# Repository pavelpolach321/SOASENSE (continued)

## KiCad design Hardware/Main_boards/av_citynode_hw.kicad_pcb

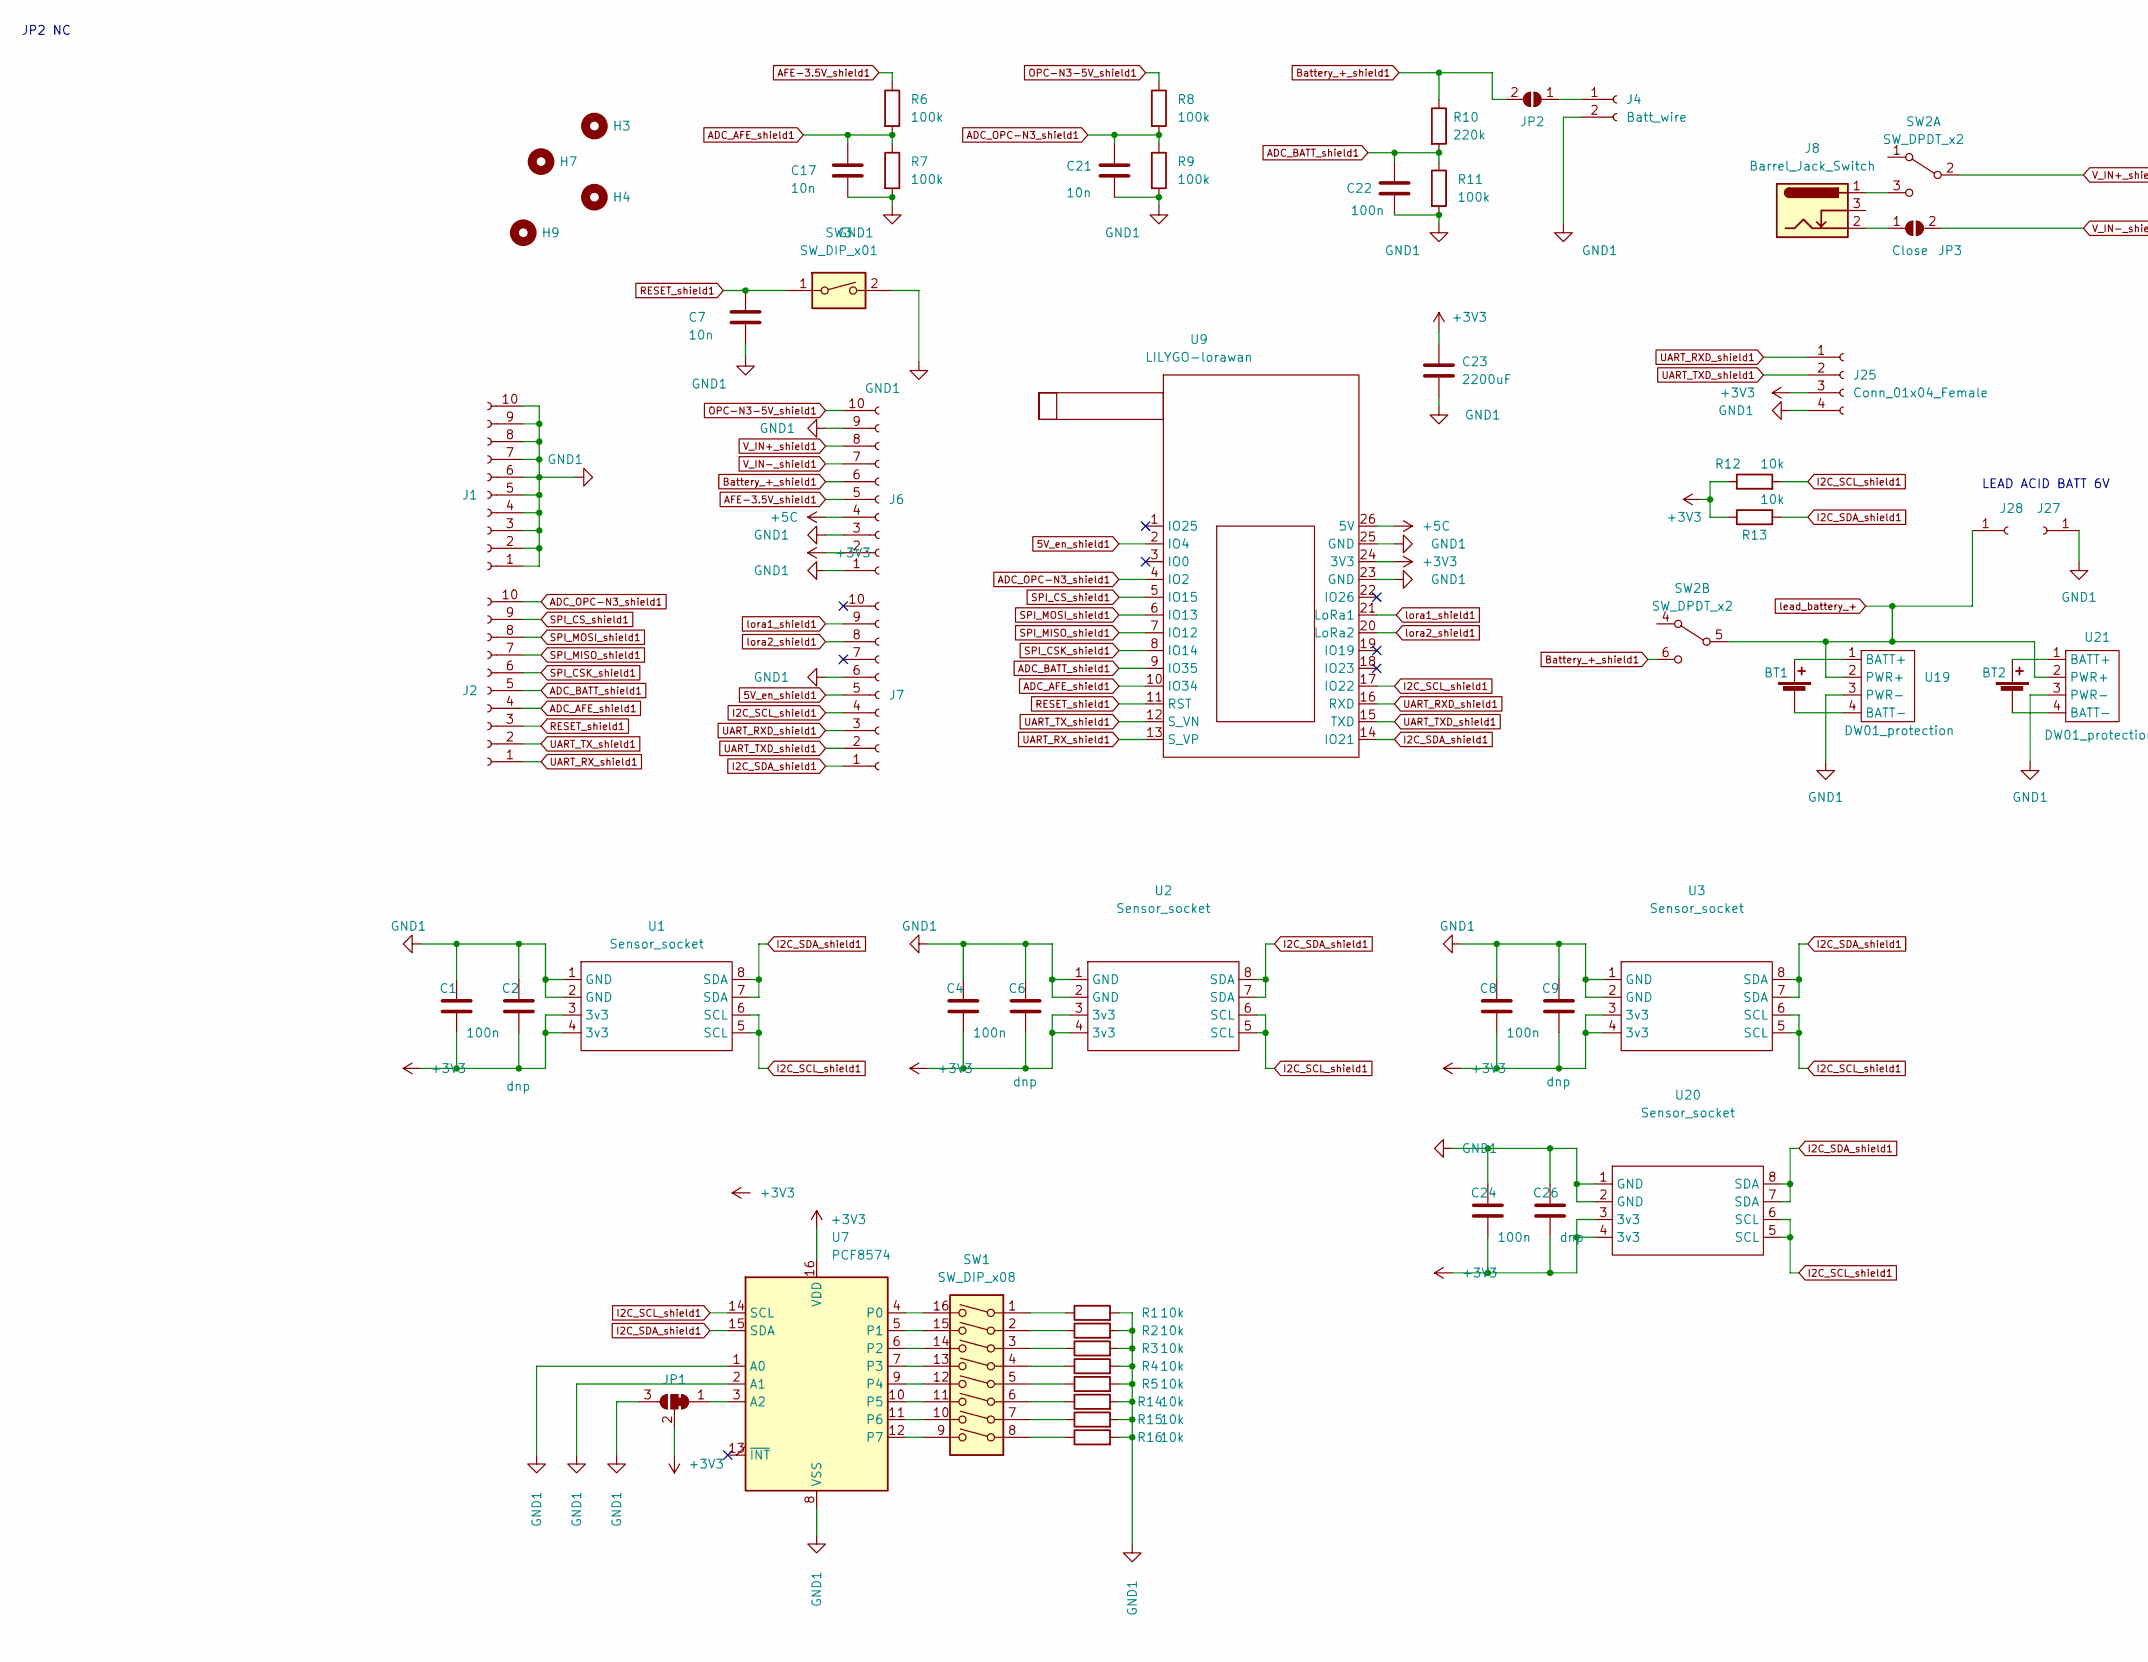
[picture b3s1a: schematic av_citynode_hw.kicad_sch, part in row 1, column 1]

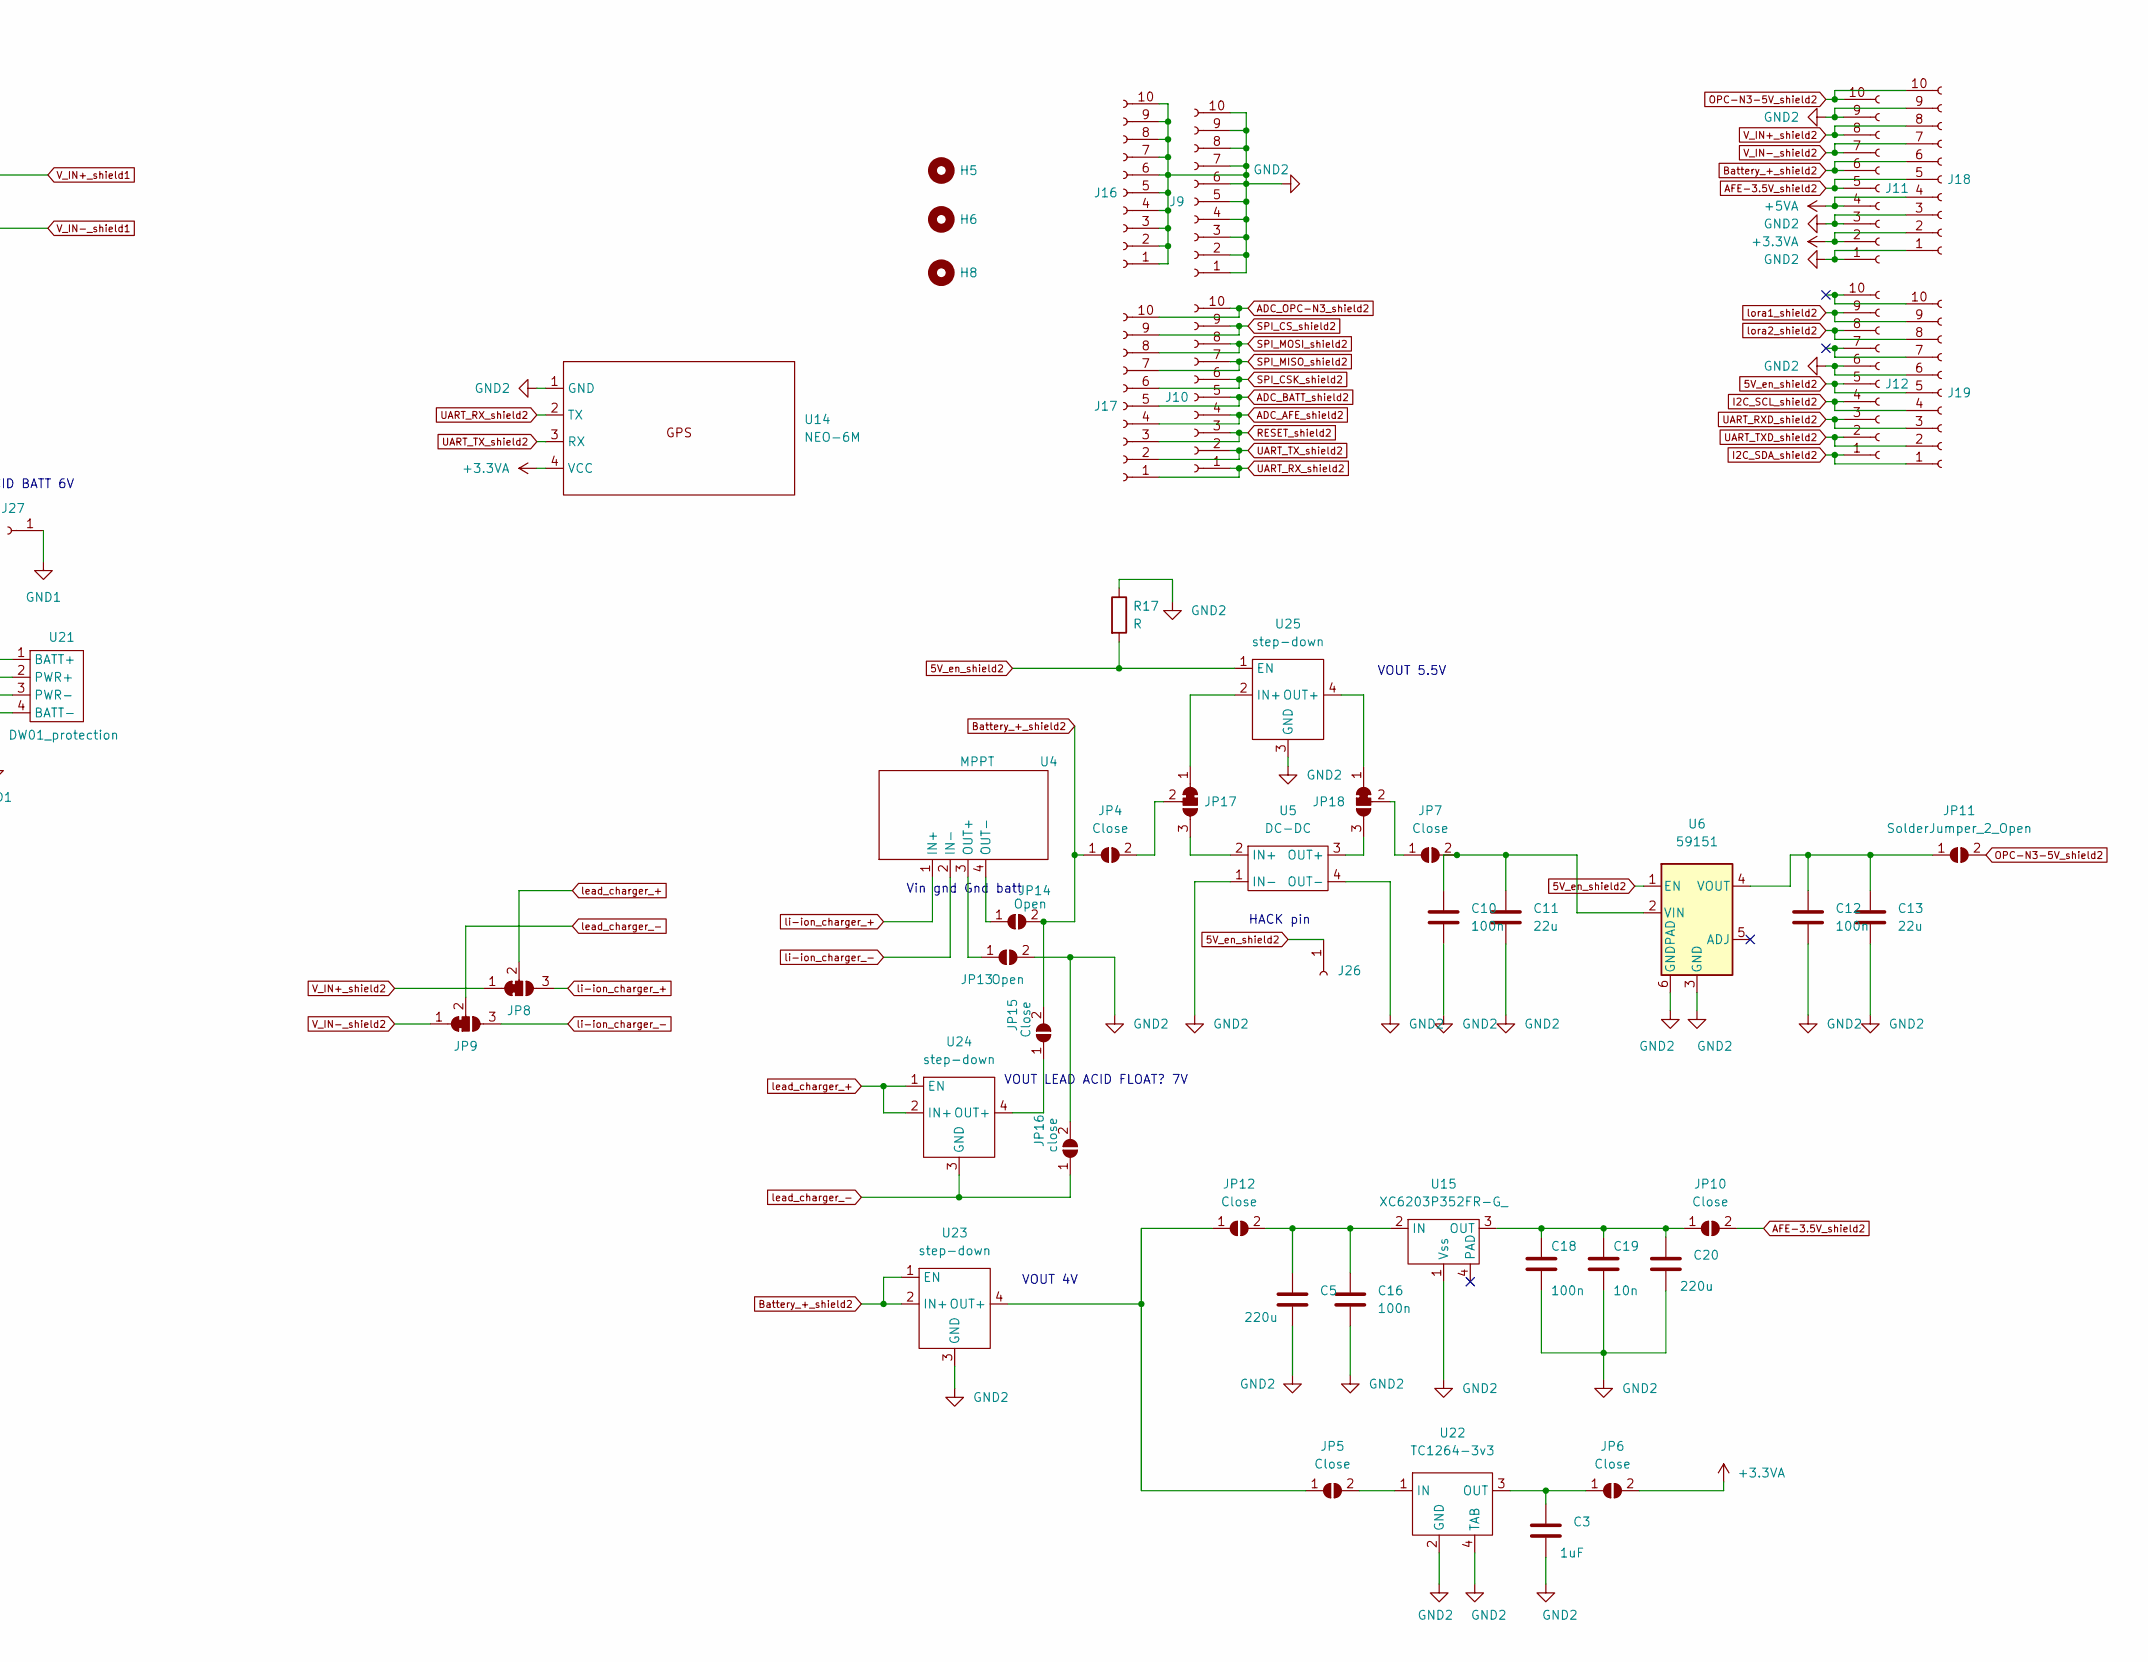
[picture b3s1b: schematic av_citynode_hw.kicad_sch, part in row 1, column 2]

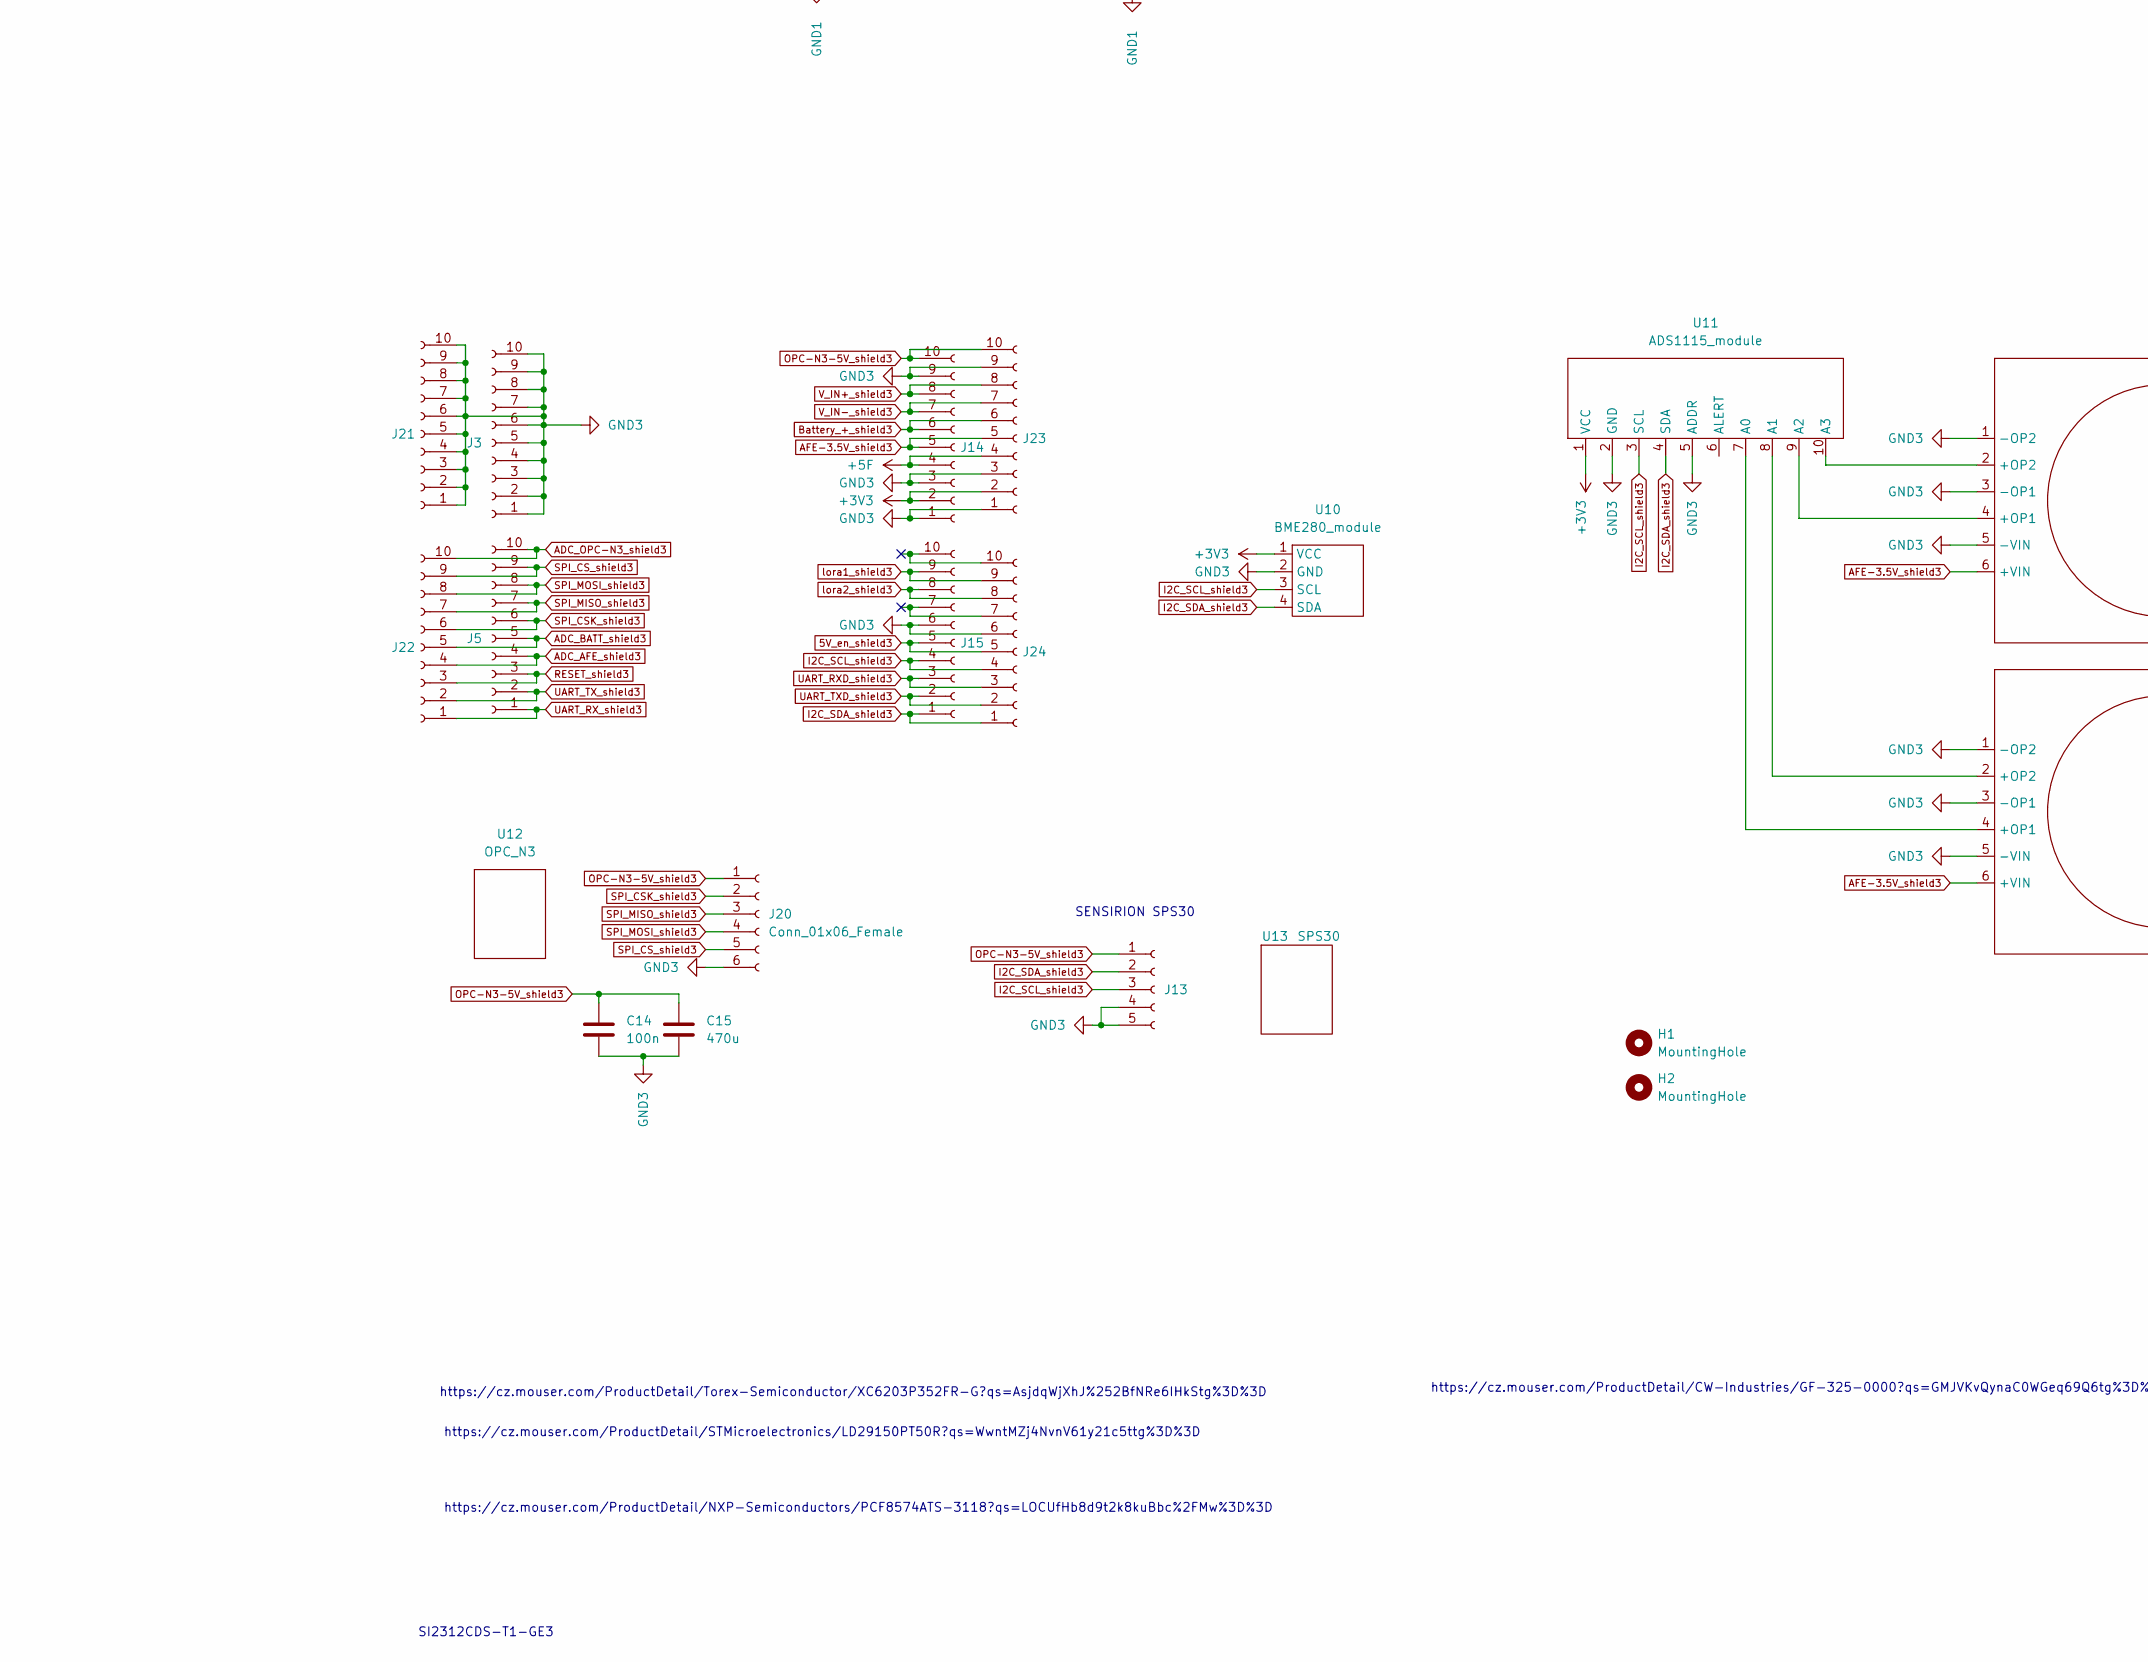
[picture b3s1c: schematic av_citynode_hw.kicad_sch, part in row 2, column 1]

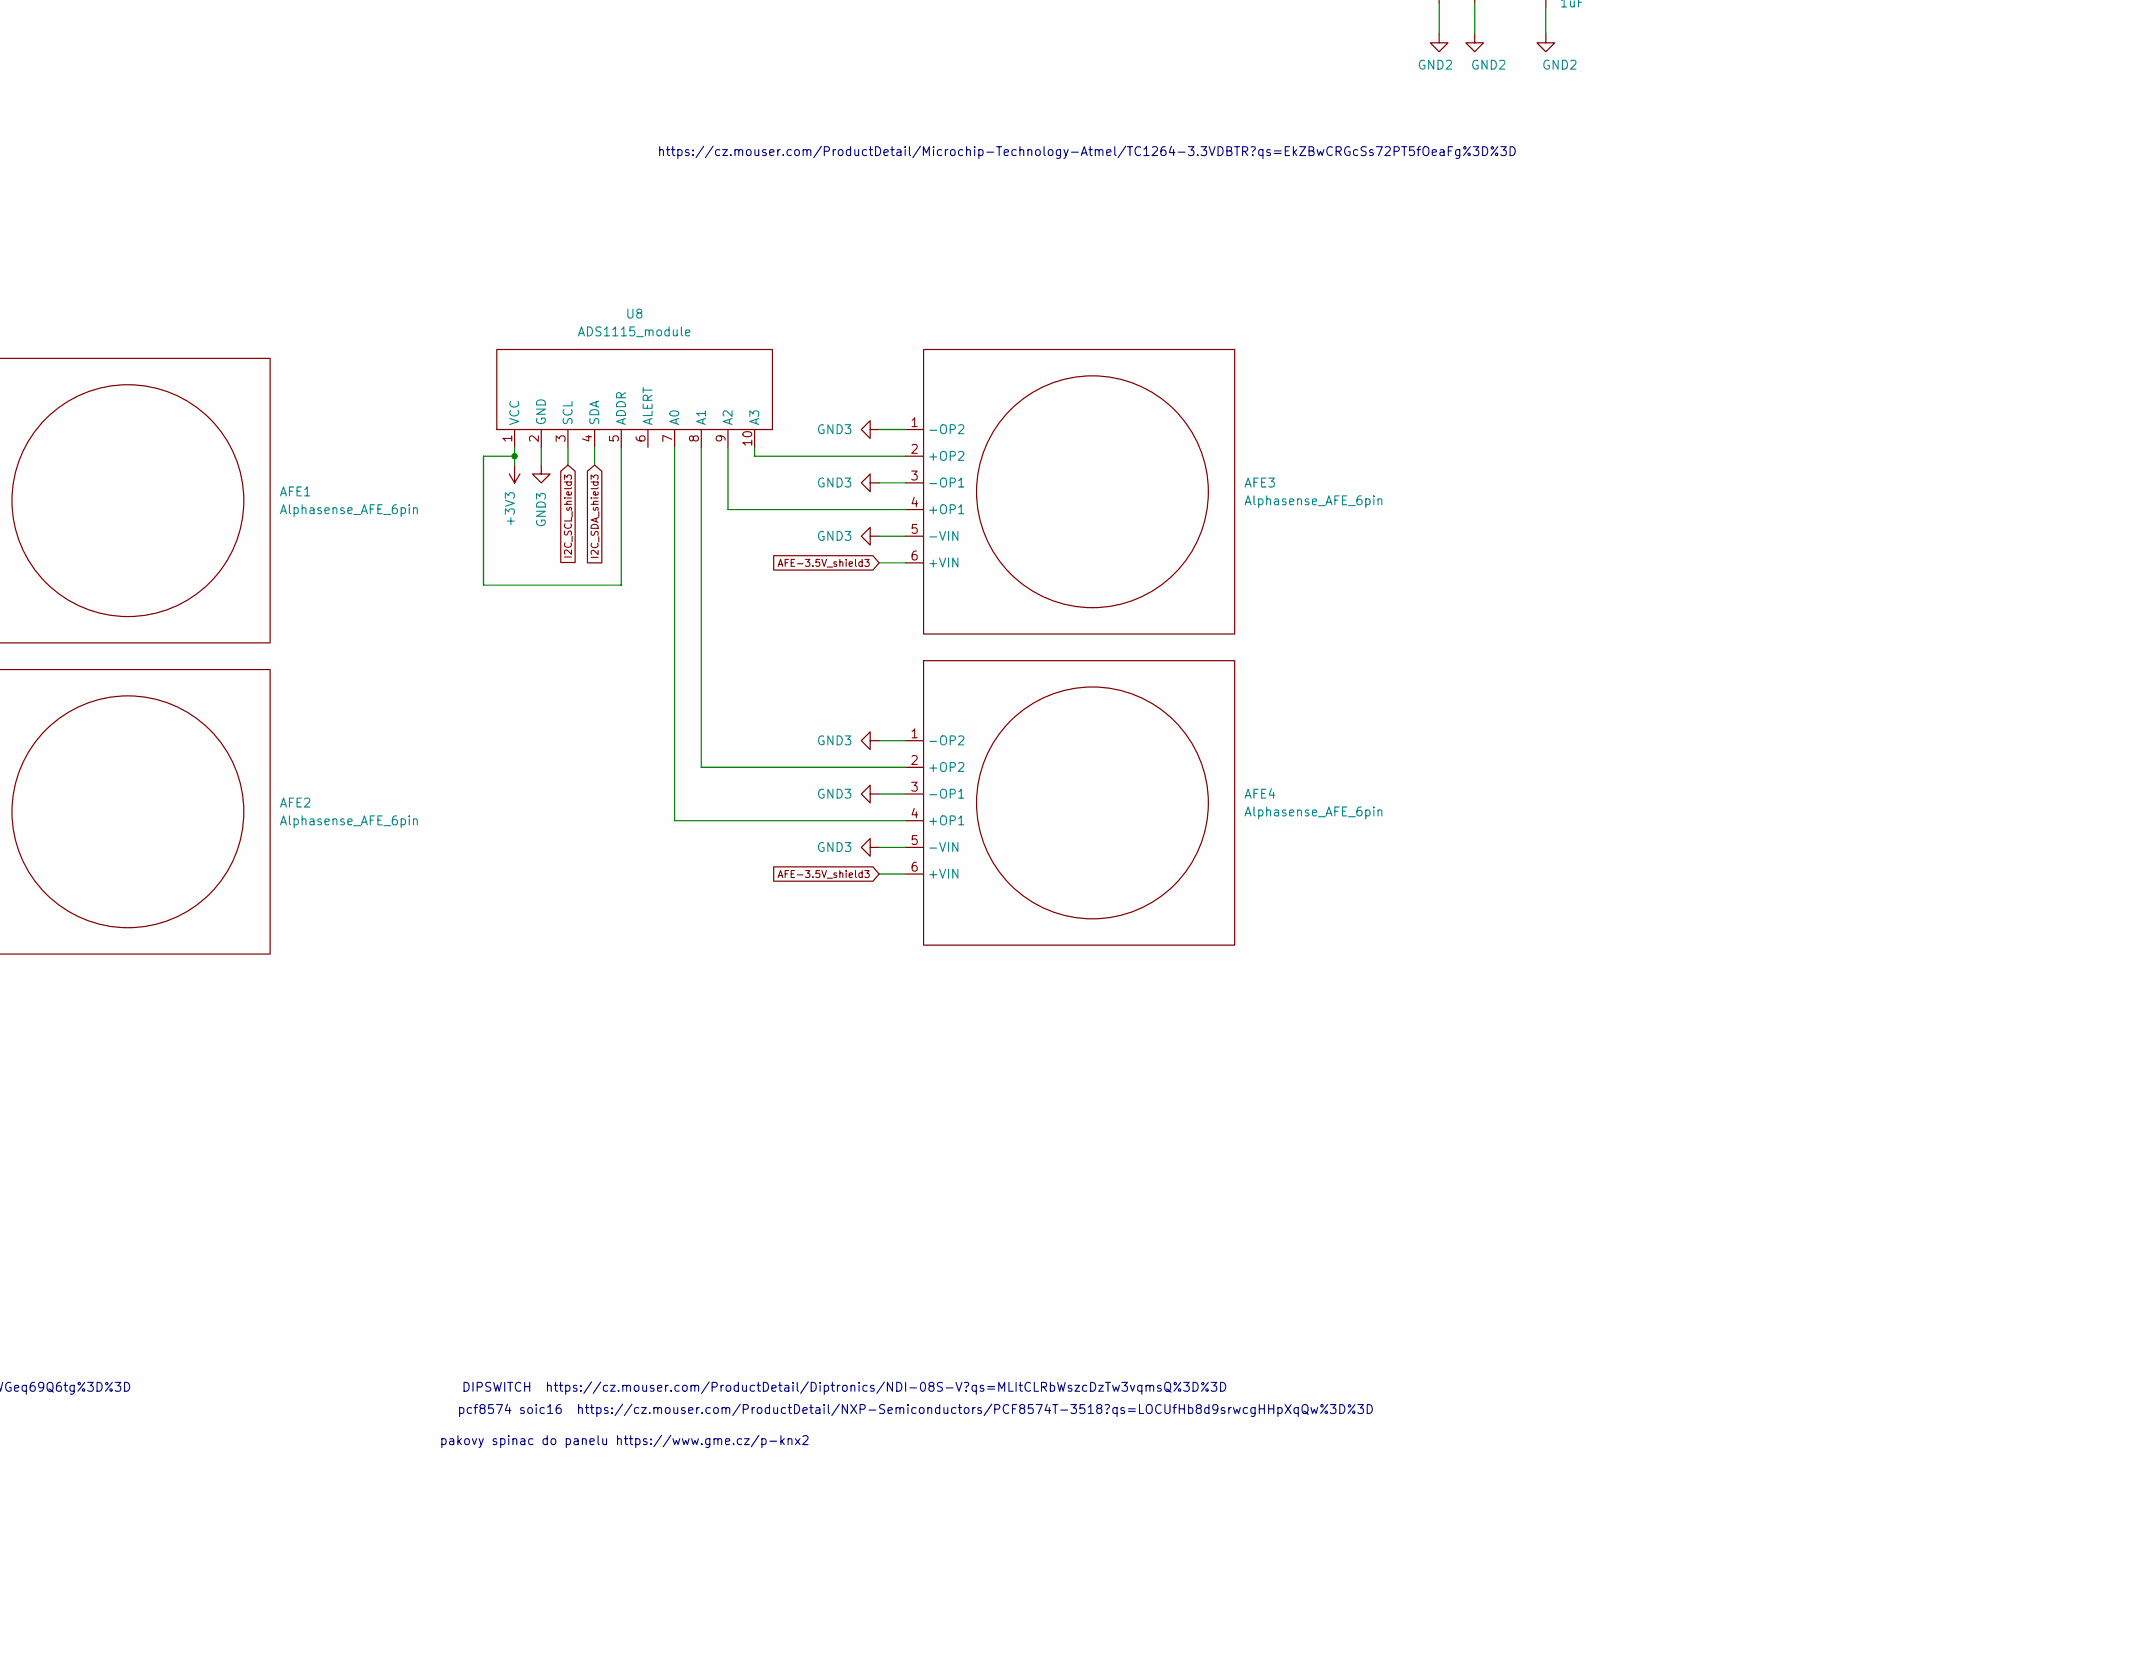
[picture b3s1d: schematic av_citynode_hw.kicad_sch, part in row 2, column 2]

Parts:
AFE1, AFE3, AFE4: Alphasense_AFE_6pin; Alphasense_AFE_6pin-LEFT
AFE2: Alphasense_AFE_6pin; Alphasense_AFE_6pin-RIGHT
BT1, BT2: Battery_Cell; BatteryHolder_MPD_BH-18650-PC2
C1, C4, C8, C24: 100n; C_0805_2012Metric_Pad1.18x1.45mm_HandSolder
C2, C6, C9, C26: dnp; C_0805_2012Metric_Pad1.18x1.45mm_HandSolder
C3: 1uF; C_0805_2012Metric_Pad1.18x1.45mm_HandSolder
C5, C20: 220u; CP_Radial_D5.0mm_P2.50mm
C7, C17, C19, C21: 10n; C_0805_2012Metric
C10, C12, C14, C16, C18, C22: 100n; C_0805_2012Metric
C11, C13: 22u; C_0805_2012Metric
C15: 470u; CP_Radial_D10.0mm_P3.50mm
C23: 2200uF; CP_Radial_D12.5mm_P5.00mm
H1, H2, H3, H4, H5, H6, H9: MountingHole; MountingHole_4.3mm_M4
H7, H8: MountingHole; opc-n3-hole
J1, J2, J3, J5, J6, J7, J9, J10, J11, J12, J14, J15, J16, J17, J18, J19, J21, J22, J23, J24: Conn_01x10_Female; PinSocket_1x10_P2.54mm_Vertical
J4: Batt_wire; PinSocket_1x02_P2.54mm_Vertical
J8: Barrel_Jack_Switch; BarrelJack_Horizontal
J13: Conn_01x05_Female; PinHeader_1x05_P2.54mm_Vertical
J20: Conn_01x06_Female; PinHeader_1x06_P2.54mm_Vertical
J25: Conn_01x04_Female; PinSocket_1x04_P2.54mm_Vertical
J26: Conn_01x01_Female; PinHeader_1x01_P2.54mm_Vertical
J27, J28: Conn_01x01_Female; PinSocket_1x01_P2.54mm_Vertical
JP1: SolderJumper_3_Bridged12; SolderJumper-3_P1.3mm_Bridged12_RoundedPad1.0x1.5mm_NumberL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
JP2: SolderJumper_2_Open; SolderJumper-2_P1.3mm_Open_RoundedPad1.0x1.5mm
JP3: Close; SolderJumper-2_P1.3mm_Bridged_Pad1.0x1.5mm
JP4, JP5, JP6, JP7, JP10, JP12, JP15: Close; SolderJumper-2_P1.3mm_Bridged_RoundedPad1.0x1.5mm
JP8, JP9, JP17, JP18: SolderJumper_3_Bridged12; SolderJumper-3_P1.3mm_Bridged12_Pad1.0x1.5mm
JP11: SolderJumper_2_Open; SolderJumper-2_P1.3mm_Bridged_RoundedPad1.0x1.5mm
JP13, JP14: Open; SolderJumper-2_P1.3mm_Open_RoundedPad1.0x1.5mm
JP16: close; SolderJumper-2_P1.3mm_Bridged_RoundedPad1.0x1.5mm
R1, R2, R3, R4, R5, R12, R13, R14, R15, R16: 10k; R_0805_2012Metric
R6, R7, R8, R9, R11: 100k; R_0805_2012Metric
R10: 220k; R_0805_2012Metric
R17: R; R_0805_2012Metric
SW1: SW_DIP_x08; SW_DIP_SPSTx08_Slide_6.7x21.88mm_W7.62mm_P2.54mm_LowProfile
SW2: SW_DPDT_x2; Switch
SW3: SW_DIP_x01; SW_PUSH_6mm
U1, U2, U3, U20: Sensor_socket; Sensor_module
U4: MPPT; DC-DC
U5: DC-DC; STEP_UP
U6: 59151; PPAK
U7: PCF8574; SOIC-16_4.55x10.3mm_P1.27mm
U8, U11: ADS1115_module; ADS1115-module
U9: LILYGO-lorawan; LILYGO-LORAWAN
U10: BME280_module; BME280-module
U12: OPC_N3; opc-n3_3holes
U13: SPS30
U14: NEO-6M; NEO-6M-mod
U15: XC6203P352FR-G_; SOT-223
U19, U21: DW01_protection
U22: TC1264-3v3; SOT-223
U23, U24, U25: step-down; mp2315-module

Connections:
5V_en_shield1: J7.5, U9.2 (IO4)
5V_en_shield2: J12.5, J19.5, J26.1, R17.2, U6.1 (EN), U25.1 (EN)
5V_en_shield3: J15.5, J24.5
+3.3VA: J11.2, J18.2, JP6.2 (B), U14.4 (VCC)
+3V3: C1.2, C2.2, C4.2, C6.2, C8.2, C9.2, C23.1, C24.2, C26.2, J6.2, J14.2, J23.2, J25.3, JP1.2 (C), R12.1, R13.1, U1.3 (3v3), U1.4 (3v3), U2.3 (3v3), U2.4 (3v3), U3.3 (3v3), U3.4 (3v3), U7.16 (VDD), U8.1 (VCC), U8.5 (ADDR), U9.24 (3V3), U10.1 (VCC), U11.1 (VCC), U20.3 (3v3), U20.4 (3v3)
+5C: J6.4, U9.26 (5V)
+5F: J14.4, J23.4
+5VA: J11.4, J18.4
ADC_AFE_shield1: C17.1, J2.4, R6.2, R7.1, U9.10 (IO34)
ADC_AFE_shield2: J10.4, J17.4
ADC_AFE_shield3: J5.4, J22.4
ADC_BATT_shield1: C22.1, J2.5, R10.2, R11.1, U9.9 (IO35)
ADC_BATT_shield2: J10.5, J17.5
ADC_BATT_shield3: J5.5, J22.5
ADC_OPC-N3_shield1: C21.1, J2.10, R8.2, R9.1, U9.4 (IO2)
ADC_OPC-N3_shield2: J10.10, J17.10
ADC_OPC-N3_shield3: J5.10, J22.10
AFE-3.5V_shield1: J6.5, R6.1
AFE-3.5V_shield2: J11.5, J18.5, JP10.2 (B)
AFE-3.5V_shield3: AFE1.6 (+VIN), AFE2.6 (+VIN), AFE3.6 (+VIN), AFE4.6 (+VIN), J14.5, J23.5
Battery_+_shield1: J6.6, JP2.2 (B), R10.1, SW2.6 (C)
Battery_+_shield2: J11.6, J18.6, JP4.1 (A), JP14.2 (B), JP15.2 (B), U23.1 (EN), U23.2 (IN+)
Battery_+_shield3: J14.6, J23.6
GND1: C1.1, C2.1, C4.1, C6.1, C7.2, C8.1, C9.1, C17.2, C21.2, C22.2, C23.2, C24.1, C26.1, J1.1, J1.2, J1.3, J1.4, J1.5, J1.6, J1.7, J1.8, J1.9, J1.10, J4.2, J6.1, J6.3, J6.9, J7.6, J25.4, J27.1, JP1.3 (B), R1.2, R2.2, R3.2, R4.2, R5.2, R7.2, R9.2, R11.2, R14.2, R15.2, R16.2, SW3.2, U1.1 (GND), U1.2 (GND), U2.1 (GND), U2.2 (GND), U3.1 (GND), U3.2 (GND), U7.1 (A0), U7.2 (A1), U7.8 (VSS), U9.23 (GND), U9.25 (GND), U19.3 (PWR-), U20.1 (GND), U20.2 (GND), U21.3 (PWR-)
GND2: C3.2, C5.2, C10.2, C11.2, C12.2, C13.2, C16.2, C18.2, C19.2, C20.2, J9.1, J9.2, J9.3, J9.4, J9.5, J9.6, J9.7, J9.8, J9.9, J9.10, J11.1, J11.3, J11.9, J12.6, J16.1, J16.2, J16.3, J16.4, J16.5, J16.6, J16.7, J16.8, J16.9, J16.10, J18.1, J18.3, J18.9, J19.6, JP13.2 (B), JP16.2 (B), R17.1, U5.1 (IN-), U5.4 (OUT-), U6.3 (GND), U6.6 (GNDPAD), U14.1 (GND), U15.1 (Vss), U22.2 (GND), U22.4 (TAB), U23.3 (GND), U25.3 (GND)
GND3: AFE1.1 (-OP2), AFE1.3 (-OP1), AFE1.5 (-VIN), AFE2.1 (-OP2), AFE2.3 (-OP1), AFE2.5 (-VIN), AFE3.1 (-OP2), AFE3.3 (-OP1), AFE3.5 (-VIN), AFE4.1 (-OP2), AFE4.3 (-OP1), AFE4.5 (-VIN), C14.2, C15.2, J3.1, J3.2, J3.3, J3.4, J3.5, J3.6, J3.7, J3.8, J3.9, J3.10, J13.4, J13.5, J14.1, J14.3, J14.9, J15.6, J20.6, J21.1, J21.2, J21.3, J21.4, J21.5, J21.6, J21.7, J21.8, J21.9, J21.10, J23.1, J23.3, J23.9, J24.6, U8.2 (GND), U10.2 (GND), U11.2 (GND), U11.5 (ADDR)
I2C_SCL_shield1: J7.4, R12.2, U1.5 (SCL), U1.6 (SCL), U2.5 (SCL), U2.6 (SCL), U3.5 (SCL), U3.6 (SCL), U7.14 (SCL), U9.17 (IO22), U20.5 (SCL), U20.6 (SCL)
I2C_SCL_shield2: J12.4, J19.4
I2C_SCL_shield3: J13.3, J15.4, J24.4, U8.3 (SCL), U10.3 (SCL), U11.3 (SCL)
I2C_SDA_shield1: J7.1, R13.2, U1.7 (SDA), U1.8 (SDA), U2.7 (SDA), U2.8 (SDA), U3.7 (SDA), U3.8 (SDA), U7.15 (SDA), U9.14 (IO21), U20.7 (SDA), U20.8 (SDA)
I2C_SDA_shield2: J12.1, J19.1
I2C_SDA_shield3: J13.2, J15.1, J24.1, U8.4 (SDA), U10.4 (SDA), U11.4 (SDA)
unnamed: AFE1.2 (+OP2), U11.10 (A3)
unnamed: AFE1.4 (+OP1), U11.9 (A2)
unnamed: AFE2.2 (+OP2), U11.8 (A1)
unnamed: AFE2.4 (+OP1), U11.7 (A0)
unnamed: AFE3.2 (+OP2), U8.10 (A3)
unnamed: AFE3.4 (+OP1), U8.9 (A2)
unnamed: AFE4.2 (+OP2), U8.8 (A1)
unnamed: AFE4.4 (+OP1), U8.7 (A0)
unnamed: BT1.1 (+), U19.1 (BATT+)
unnamed: BT1.2 (-), U19.4 (BATT-)
unnamed: BT2.1 (+), U21.1 (BATT+)
unnamed: BT2.2 (-), U21.4 (BATT-)
unnamed: C3.1, JP6.1 (A), U22.3 (OUT)
unnamed: C10.1, C11.1, JP7.2 (B), U6.2 (VIN)
unnamed: C12.1, C13.1, JP11.1 (A), U6.4 (VOUT)
unnamed: C5.1, C16.1, JP12.2 (B), U15.2 (IN)
unnamed: C18.1, C19.1, C20.1, JP10.1 (A), U15.3 (OUT)
unnamed: J4.1, JP2.1 (A)
unnamed: J8.1, SW2.3 (C)
unnamed: J8.2, JP3.1 (A)
unnamed: JP1.1 (A), U7.3 (A2)
unnamed: JP5.2 (B), U22.1 (IN)
unnamed: JP5.1 (A), JP12.1 (A), U23.4 (OUT+)
unnamed: JP13.1 (A), U4.3 (OUT+)
unnamed: JP14.1 (A), U4.4 (OUT-)
unnamed: JP15.1 (A), U24.4 (OUT+)
unnamed: JP17.1 (A), U25.2 (IN+)
unnamed: JP4.2 (B), JP17.2 (C)
unnamed: JP17.3 (B), U5.2 (IN+)
unnamed: JP18.1 (A), U25.4 (OUT+)
unnamed: JP7.1 (A), JP18.2 (C)
unnamed: JP18.3 (B), U5.3 (OUT+)
unnamed: R1.1, SW1.1
unnamed: R2.1, SW1.2
unnamed: R3.1, SW1.3
unnamed: R4.1, SW1.4
unnamed: R5.1, SW1.5
unnamed: R14.1, SW1.6
unnamed: R15.1, SW1.7
unnamed: R16.1, SW1.8
unnamed: SW1.9, U7.12 (P7)
unnamed: SW1.10, U7.11 (P6)
unnamed: SW1.11, U7.10 (P5)
unnamed: SW1.12, U7.9 (P4)
unnamed: SW1.13, U7.7 (P3)
unnamed: SW1.14, U7.6 (P2)
unnamed: SW1.15, U7.5 (P1)
unnamed: SW1.16, U7.4 (P0)
OPC-N3-5V_shield1: J6.10, R8.1
OPC-N3-5V_shield2: J11.10, J18.10, JP11.2 (B)
OPC-N3-5V_shield3: C14.1, C15.1, J13.1, J14.10, J20.1, J23.10
RESET_shield1: C7.1, J2.3, SW3.1, U9.11 (RST)
RESET_shield2: J10.3, J17.3
RESET_shield3: J5.3, J22.3
SPI_CSK_shield1: J2.6, U9.8 (IO14)
SPI_CSK_shield2: J10.6, J17.6
SPI_CSK_shield3: J5.6, J20.2, J22.6
SPI_CS_shield1: J2.9, U9.5 (IO15)
SPI_CS_shield2: J10.9, J17.9
SPI_CS_shield3: J5.9, J20.5, J22.9
SPI_MISO_shield1: J2.7, U9.7 (IO12)
SPI_MISO_shield2: J10.7, J17.7
SPI_MISO_shield3: J5.7, J20.3, J22.7
SPI_MOSI_shield1: J2.8, U9.6 (IO13)
SPI_MOSI_shield2: J10.8, J17.8
SPI_MOSI_shield3: J5.8, J20.4, J22.8
UART_RXD_shield1: J7.3, J25.1, U9.16 (RXD)
UART_RXD_shield2: J12.3, J19.3
UART_RXD_shield3: J15.3, J24.3
UART_RX_shield1: J2.1, U9.13 (S_VP)
UART_RX_shield2: J10.1, J17.1, U14.2 (TX)
UART_RX_shield3: J5.1, J22.1
UART_TXD_shield1: J7.2, J25.2, U9.15 (TXD)
UART_TXD_shield2: J12.2, J19.2
UART_TXD_shield3: J15.2, J24.2
UART_TX_shield1: J2.2, U9.12 (S_VN)
UART_TX_shield2: J10.2, J17.2, U14.3 (RX)
UART_TX_shield3: J5.2, J22.2
V_IN+_shield1: J6.8, SW2.2 (B)
V_IN+_shield2: J11.8, J18.8, JP8.1 (A)
V_IN+_shield3: J14.8, J23.8
V_IN-_shield1: J6.7, JP3.2 (B)
V_IN-_shield2: J11.7, J18.7, JP9.1 (A)
V_IN-_shield3: J14.7, J23.7
lead_battery_+: J28.1, SW2.5 (B), U19.2 (PWR+), U21.2 (PWR+)
lead_charger_+: JP8.2 (C), U24.1 (EN), U24.2 (IN+)
lead_charger_-: JP9.2 (C), JP16.1 (A), U24.3 (GND)
li-ion_charger_+: JP8.3 (B), U4.1 (IN+)
li-ion_charger_-: JP9.3 (B), U4.2 (IN-)
lora1_shield1: J7.9, U9.21 (LoRa1)
lora1_shield2: J12.9, J19.9
lora1_shield3: J15.9, J24.9
lora2_shield1: J7.8, U9.20 (LoRa2)
lora2_shield2: J12.8, J19.8
lora2_shield3: J15.8, J24.8

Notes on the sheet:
pakovy spinac do panelu https://www.gme.cz/p-knx2
https://cz.mouser.com/ProductDetail/NXP-Semiconductors/PCF8574ATS-3118?qs=LOCUfHb8d9t2k8kuBbc%2FMw%3D%3D
Vin gnd Gnd batt
DIPSWITCH https://cz.mouser.com/ProductDetail/Diptronics/NDI-08S-V?qs=MLItCLRbWszcDzTw3vqmsQ%3D%3D
VOUT 4V
JP2 NC
SI2312CDS-T1-GE3
pcf8574 soic16 https://cz.mouser.com/ProductDetail/NXP-Semiconductors/PCF8574T-3518?qs=LOCUfHb8d9srwcgHHpXqQw%3D%3D
https://cz.mouser.com/ProductDetail/CW-Industries/GF-325-0000?qs=GMJVKvQynaC0WGeq69Q6tg%3D%3D
https://cz.mouser.com/ProductDetail/STMicroelectronics/LD29150PT50R?qs=WwntMZj4NvnV61y21c5ttg%3D%3D
VOUT LEAD ACID FLOAT? 7V
SENSIRION SPS30
https://cz.mouser.com/ProductDetail/Microchip-Technology-Atmel/TC1264-3.3VDBTR?qs=EkZBwCRGcSs72PT5fOeaFg%3D%3D
https://cz.mouser.com/ProductDetail/Torex-Semiconductor/XC6203P352FR-G?qs=AsjdqWjXhJ%252BfNRe6IHkStg%3D%3D
VOUT 5.5V
HACK pin
LEAD ACID BATT 6V

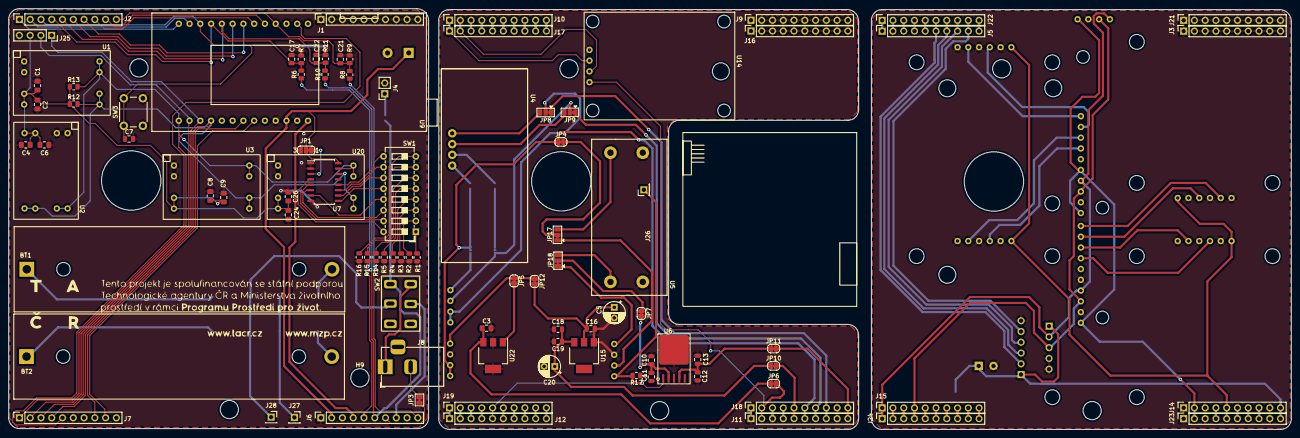
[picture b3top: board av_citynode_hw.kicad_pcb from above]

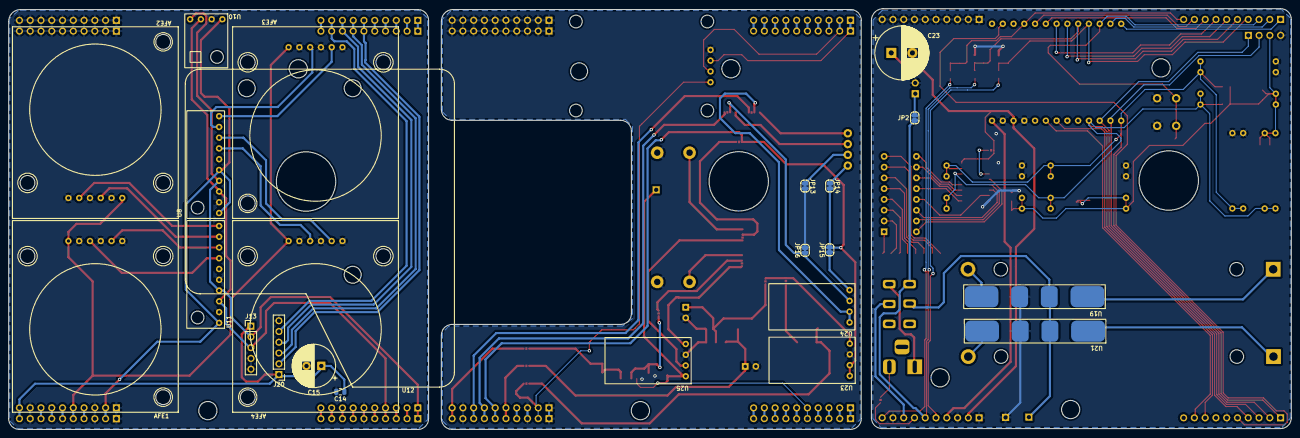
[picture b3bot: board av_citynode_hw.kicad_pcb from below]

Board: 2 copper layers, 302.6 x 99.3 mm, 128 parts (23 on the bottom side), 127 nets.

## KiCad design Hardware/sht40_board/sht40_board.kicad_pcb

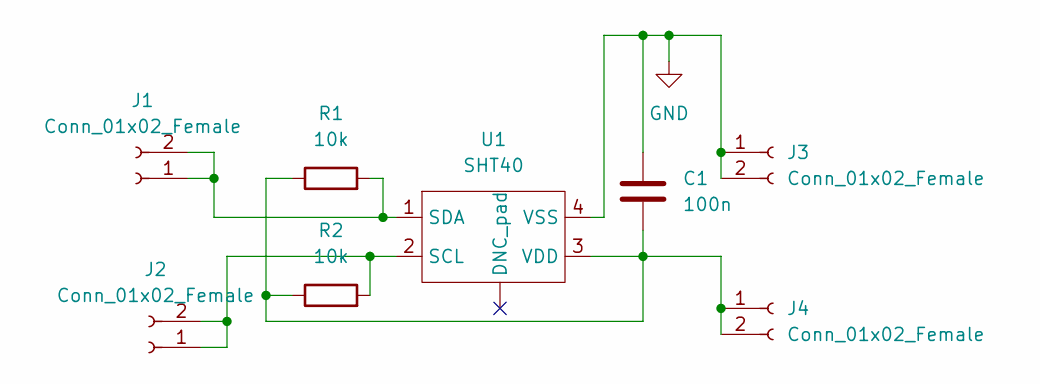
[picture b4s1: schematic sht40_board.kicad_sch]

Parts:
C1: 100n; C_0805_2012Metric
J1, J2, J3, J4: Conn_01x02_Female; PinHeader_1x02_P2.54mm_Vertical
R1, R2: 10k; R_0805_2012Metric
U1: SHT40

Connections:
GND: C1.1, J3.1, J3.2, U1.4 (VSS)
unnamed: C1.2, J4.1, J4.2, R1.1, R2.1, U1.3 (VDD)
unnamed: J1.1, J1.2, R1.2, U1.1 (SDA)
unnamed: J2.1, J2.2, R2.2, U1.2 (SCL)

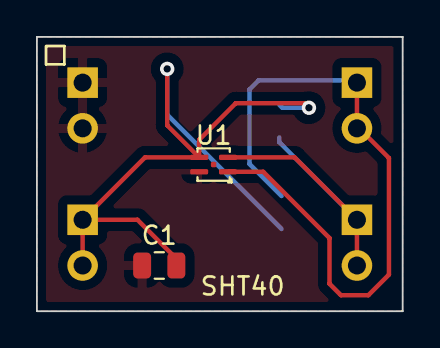
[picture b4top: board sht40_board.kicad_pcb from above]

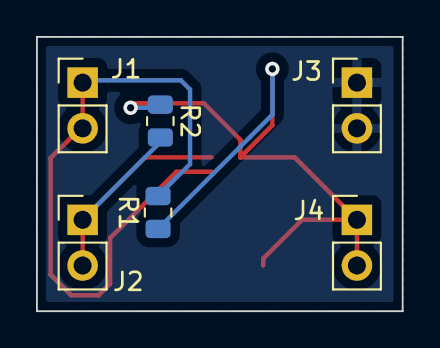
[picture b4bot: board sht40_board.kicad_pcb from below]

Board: 2 copper layers, 20.3 x 15.2 mm, 8 parts (6 on the bottom side), 4 nets.
